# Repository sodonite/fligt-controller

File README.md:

Flight Controller
This is a custom flight controller engineered specifically for rocket stabilization and control. Powered by an STM32F722 microcontroller, it incorporates an ICM-45686 IMU alongside a BMP580 barometer, with an integrated microSD card slot dedicated to flight telemetry logging. The board supports 2S LiPo battery configurations featuring onboard charging functionality, as well as dedicated PWM output channels for servo actuation.

Designed in KiCad, the entire project is completely open source.

PCB:

3D Image:

Schematic:

Technical Specifications
Brain: STM32F722RET6 microcontroller.
IMU: ICM-45686 high-precision motion sensor.
Barometer: BMP580 altitude tracker.
Actuation: Multi-channel servo output via PWM.
Data Logging: Onboard MicroSD card slot.
Power Management:
BQ25883: 2-cell LiPo battery charger via USB-C.
TPS63070: 5V Buck-Boost regulator for servos.
LMR51430: 3.3V Buck regulator for the MCU and sensors.
D2: RGB LED (Common Anode) — Visual status indicator for system initialization, ready-to-fly state, and critical error reporting (IMU, battery, SD card, and power rails).

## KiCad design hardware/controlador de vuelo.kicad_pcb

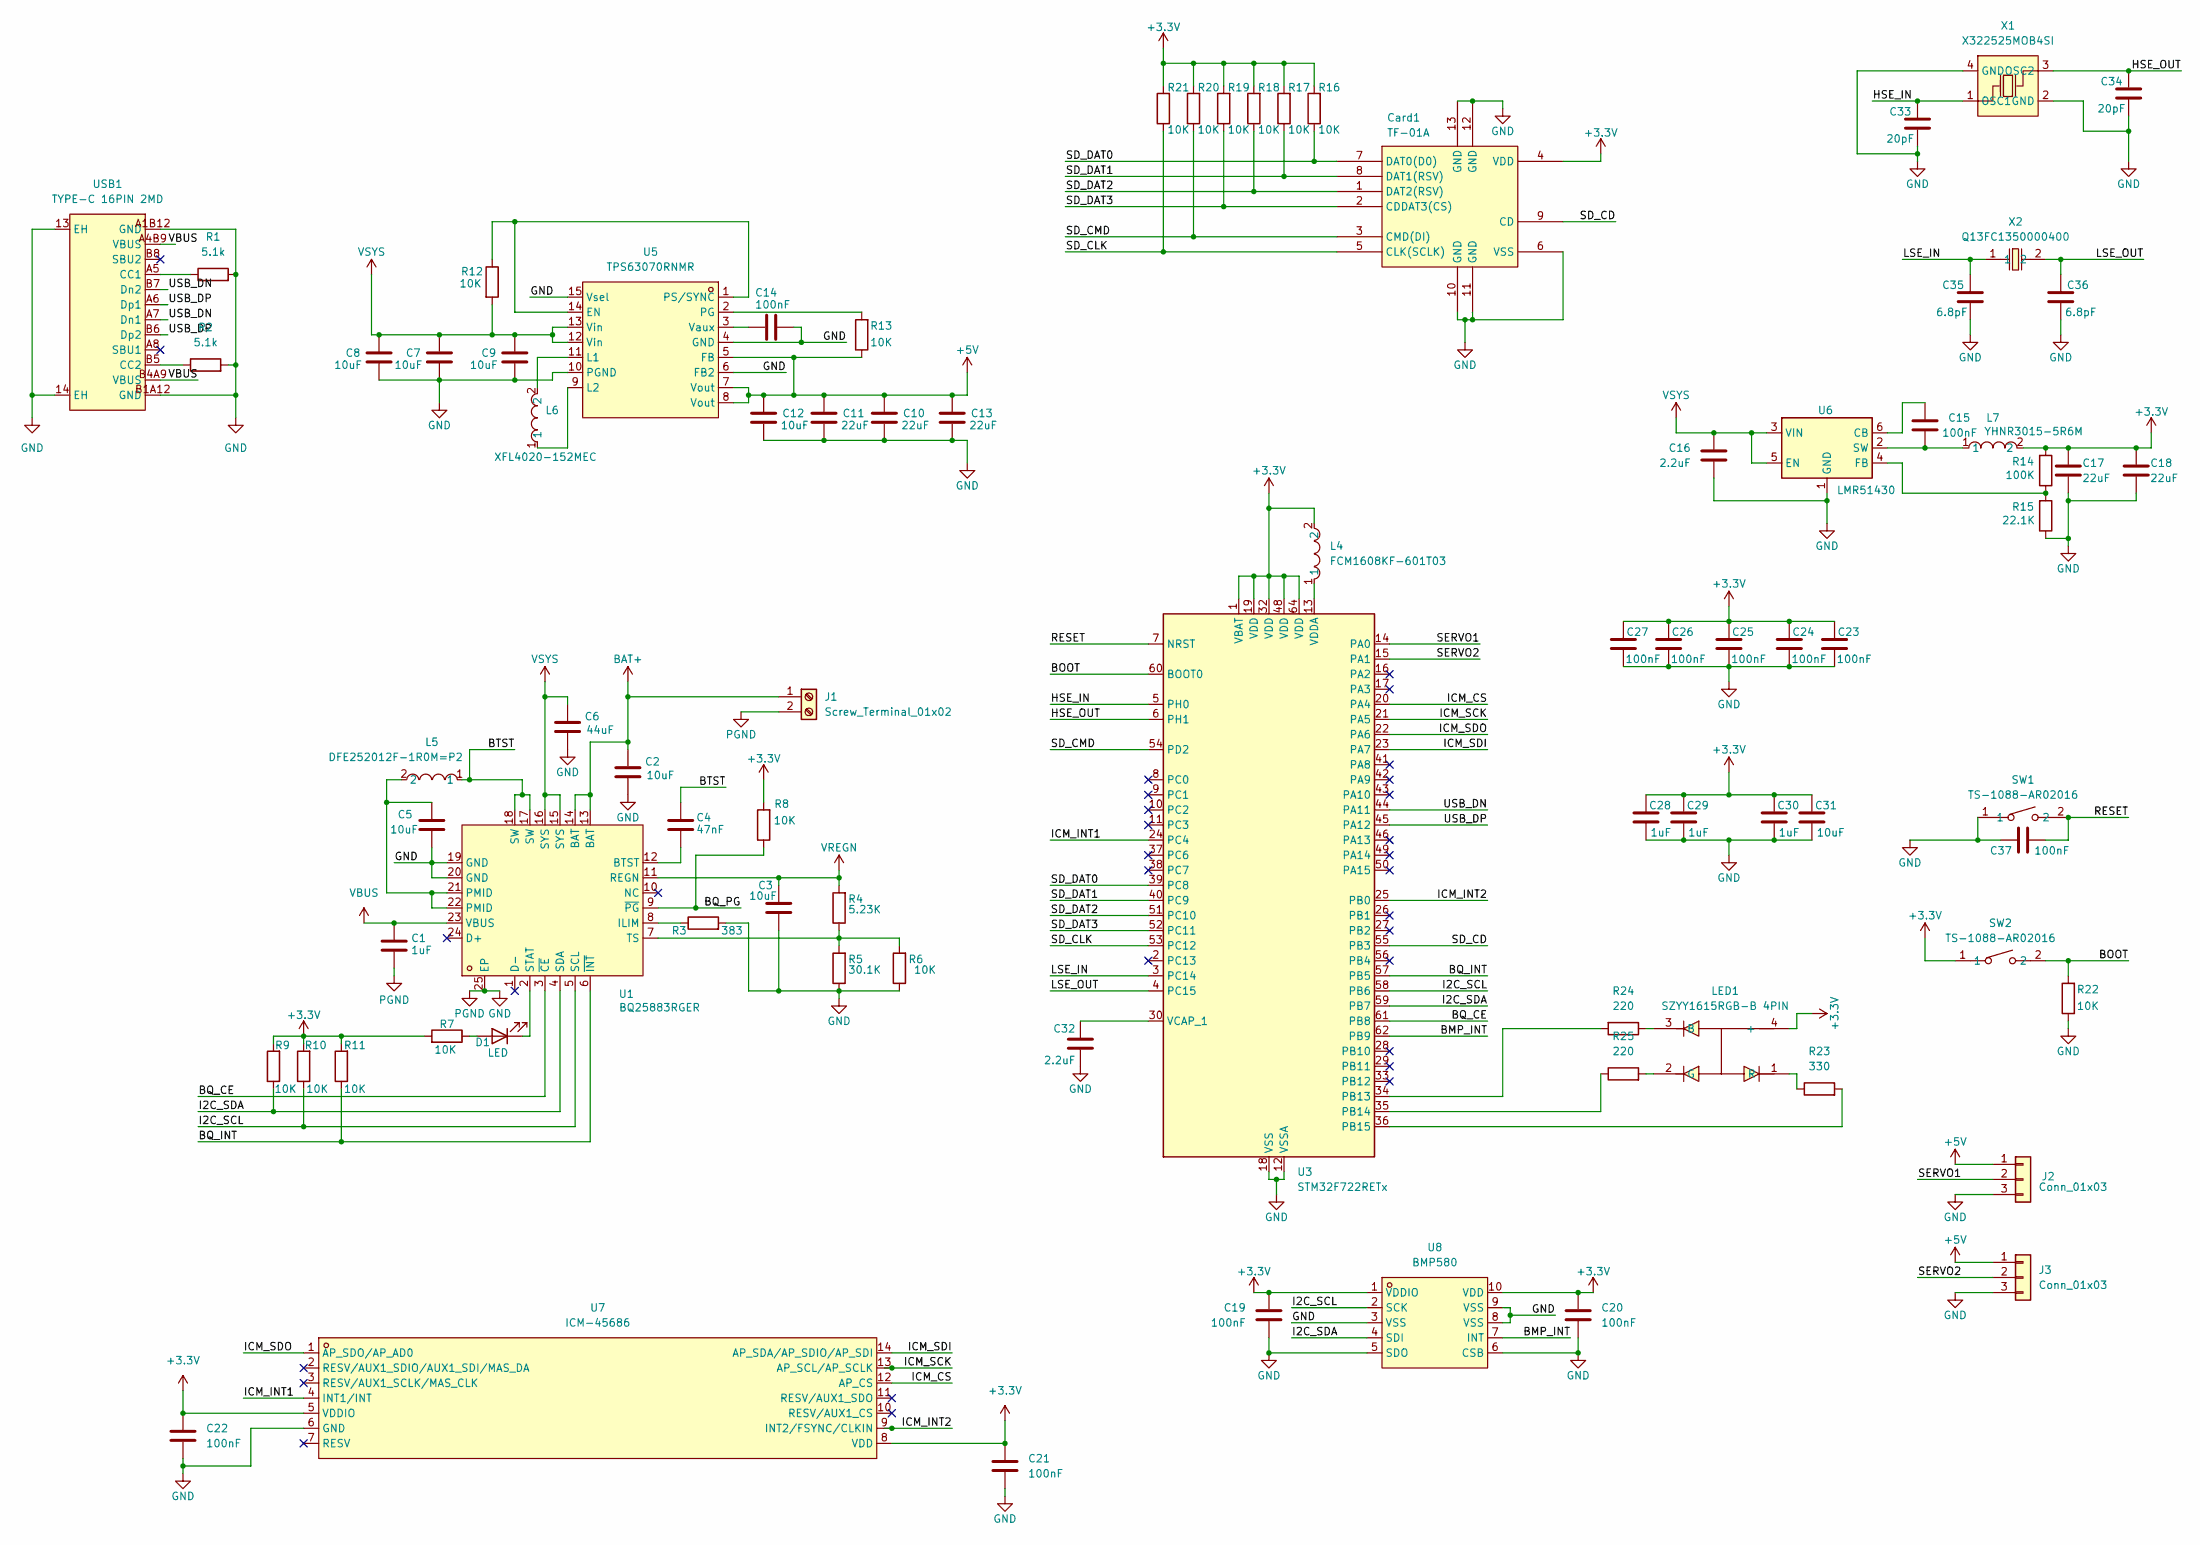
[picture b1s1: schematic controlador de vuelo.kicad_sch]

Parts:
C1, C28, C29, C30: 1uF; C_0402_1005Metric
C2, C9, C12: 10uF; C_0603_1608Metric
C3, C5, C31: 10uF; C_0402_1005Metric
C4: 47nF; C_0201_0603Metric
C6: 44uF; C_0603_1608Metric
C7, C8: 10uF; C_0805_2012Metric
C10, C11, C13: 22uF; C_0805_2012Metric
C14, C15, C19, C20, C21, C22, C23, C24, C25, C26, C27, C37: 100nF; C_0201_0603Metric
C16: 2.2uF; C_0603_1608Metric
C17, C18: 22uF; C_0402_1005Metric
C32: 2.2uF; C_0201_0603Metric
C33, C34: 20pF; C_0201_0603Metric
C35, C36: 6.8pF; C_0201_0603Metric
Card1: TF-01A; TF-SMD_TF-01A; LCSC Part C91145
D1: LED; LED_0402_1005Metric
J1: Screw_Terminal_01x02; TerminalBlock_Xinya_XY308-2.54-2P_1x02_P2.54mm_Horizontal
J2, J3: Conn_01x03; PinHeader_1x03_P2.54mm_Vertical
L4: FCM1608KF-601T03; L0603; LCSC Part C141723
L5: DFE252012F-1R0M=P2; L2520; LCSC Part C435392
L6: XFL4020-152MEC; IND-SMD_L4.0-W4.0-A; LCSC Part C3033018
L7: YHNR3015-5R6M; IND-SMD_L3.0-W3.0; LCSC Part C18236327
LED1: SZYY1615RGB-B 4PIN; LED-SMD_4P-L1.6-W1.5-TR-1; MPN SZYY1615RGB-B 4pin; LCSC Part C3029071
R1, R2: 5.1k; R_0201_0603Metric
R3: 383; R_0201_0603Metric
R4: 5.23K; R_0201_0603Metric
R5: 30.1K; R_0201_0603Metric
R6, R7, R8, R9, R10, R11, R12, R13, R16, R17, R18, R19, R20, R21, R22: 10K; R_0201_0603Metric
R14: 100K; R_0402_1005Metric
R15: 22.1K; R_0402_1005Metric
R23: 330; R_0201_0603Metric
R24, R25: 220; R_0201_0603Metric
SW1, SW2: TS-1088-AR02016; SW-SMD_L3.9-W3.0-P4.45; LCSC Part C720477
U1: BQ25883RGER; VFQFPN-24_L4.0-W4.0-P0.50-BL-EP2.8; LCSC Part C544362
U3: STM32F722RETx; LQFP-64_10x10mm_P0.5mm
U5: TPS63070RNMR; VQFN-HR-15_L3.0-W2.5-P0.50-BL_TPS63070RNMR; LCSC Part C109322
U6: LMR51430; SOT-23-6
U7: ICM-45686; LGA-14_L3.0-W2.5-P0.50-TL; LCSC Part C22459454
U8: BMP580; LGA-10_L2.0-W2.0-P0.50-TL_BMP580; LCSC Part C22391138
USB1: TYPE-C 16PIN 2MD; USB-C-SMD_TYPE-C-16PIN-2MD-073; MPN TYPE-C 16PIN 2MD(073); LCSC Part C2765186
X1: X322525MOB4SI; CRYSTAL-SMD_4P-L3.2-W2.5-BL; LCSC Part C9006
X2: Q13FC1350000400; FC-135R_L3.2-W1.5; LCSC Part C32346

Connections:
+3.3V: C17.1, C18.1, C19.1, C20.1, C21.1, C22.1, C23.1, C24.1, C25.1, C26.1, C27.1, C28.1, C29.1, C30.1, C31.1, Card1.4 (VDD), L4.2, L7.2, LED1.4 (+), R7.2, R8.2, R9.2, R10.2, R11.2, R14.2, R16.2, R17.2, R18.2, R19.2, R20.2, R21.2, SW2.1, U3.1 (VBAT), U3.19 (VDD), U3.32 (VDD), U3.48 (VDD), U3.64 (VDD), U7.5 (VDDIO), U7.8 (VDD), U8.1 (VDDIO), U8.10 (VDD)
+5V: C10.1, C11.1, C12.1, C13.1, J2.1, J3.1, R13.1, U5.5 (FB), U5.7 (Vout), U5.8 (Vout)
/BMP_INT: U3.62 (PB9), U8.7 (INT)
/BOOT: R22.2, SW2.2, U3.60 (BOOT0)
/BQ_CE: U1.3 (~CE), U3.61 (PB8)
/BQ_INT: R11.1, U1.6 (~INT), U3.57 (PB5)
/BQ_PG: R8.1, U1.9 (~PG)
/BTST: C4.1, L5.1, U1.17 (SW), U1.18 (SW)
/HSE_IN: C33.1, U3.5 (PH0), X1.1 (OSC1)
/HSE_OUT: C34.1, U3.6 (PH1), X1.3 (OSC2)
/I2C_SCL: R10.1, U1.5 (SCL), U3.58 (PB6), U8.2 (SCK)
/I2C_SDA: R9.1, U1.4 (SDA), U3.59 (PB7), U8.4 (SDI)
/ICM_CS: U3.20 (PA4), U7.12 (AP_CS)
/ICM_INT1: U3.24 (PC4), U7.4 (INT1/INT)
/ICM_INT2: U3.25 (PB0), U7.9 (INT2/FSYNC/CLKIN)
/ICM_SCK: U3.21 (PA5), U7.13 (AP_SCL/AP_SCLK)
/ICM_SDI: U3.23 (PA7), U7.14 (AP_SDA/AP_SDIO/AP_SDI)
/ICM_SDO: U3.22 (PA6), U7.1 (AP_SDO/AP_AD0)
/LSE_IN: C35.1, U3.3 (PC14), X2.1
/LSE_OUT: C36.1, U3.4 (PC15), X2.2
/RESET: C37.2, SW1.2, U3.7 (NRST)
/SD_CD: Card1.9 (CD), U3.55 (PB3)
/SD_CLK: Card1.5 (CLK(SCLK)), R21.1, U3.53 (PC12)
/SD_CMD: Card1.3 (CMD(DI)), R20.1, U3.54 (PD2)
/SD_DAT0: Card1.7 (DAT0(D0)), R16.1, U3.39 (PC8)
/SD_DAT1: Card1.8 (DAT1(RSV)), R17.1, U3.40 (PC9)
/SD_DAT2: Card1.1 (DAT2(RSV)), R18.1, U3.51 (PC10)
/SD_DAT3: Card1.2 (CDDAT3(CS)), R19.1, U3.52 (PC11)
/SERVO1: J2.2, U3.14 (PA0)
/SERVO2: J3.2, U3.15 (PA1)
/USB_DN: U3.44 (PA11), USB1.A7 (Dn1), USB1.B7 (Dn2)
/USB_DP: U3.45 (PA12), USB1.A6 (Dp1), USB1.B6 (Dp2)
BAT+: C2.1, J1.1, U1.13 (BAT), U1.14 (BAT)
GND: C1.2, C2.2, C3.2, C5.2, C6.2, C7.2, C8.2, C9.2, C10.2, C11.2, C12.2, C13.2, C14.2, C16.2, C17.2, C18.2, C19.2, C20.2, C21.2, C22.2, C23.2, C24.2, C25.2, C26.2, C27.2, C28.2, C29.2, C30.2, C31.2, C32.2, C33.2, C34.2, C35.2, C36.2, C37.1, Card1.6 (VSS), Card1.10 (GND), Card1.11 (GND), Card1.12 (GND), Card1.13 (GND), J1.2, J2.3, J3.3, R1.2, R2.2, R3.2, R5.1, R6.1, R15.1, R22.1, SW1.1, U1.19 (GND), U1.20 (GND), U1.25 (EP), U3.12 (VSSA), U3.18 (VSS), U3.31 (VSS), U3.47 (VSS), U3.63 (VSS), U5.4 (GND), U5.6 (FB2), U5.10 (PGND), U5.15 (Vsel), U6.1 (GND), U7.6 (GND), U8.3 (VSS), U8.5 (SDO), U8.6 (CSB), U8.8 (VSS), U8.9 (VSS), USB1.13 (EH), USB1.14 (EH), USB1.A1B12 (GND), USB1.B1A12 (GND), X1.2 (GND), X1.4 (GND)
unnamed: C5.1, L5.2, U1.21 (PMID), U1.22 (PMID)
unnamed: D1.2 (A), R7.1
unnamed: D1.1 (K), U1.2 (STAT)
unnamed: LED1.3 (B), R24.1
unnamed: LED1.2 (G), R25.2
unnamed: LED1.1 (R), R23.1
unnamed: C4.2, U1.12 (BTST)
unnamed: R3.1, U1.8 (ILIM)
unnamed: R4.1, R5.2, R6.2, U1.7 (TS)
unnamed: R24.2, U3.34 (PB13)
unnamed: R25.1, U3.35 (PB14)
unnamed: R23.2, U3.36 (PB15)
unnamed: C32.1, U3.30 (VCAP_1)
unnamed: L4.1, U3.13 (VDDA)
unnamed: R12.1, U5.1 (PS/SYNC), U5.14 (EN)
unnamed: L6.2, U5.11 (L1)
unnamed: L6.1, U5.9 (L2)
unnamed: R13.2, U5.2 (PG)
unnamed: C14.1, U5.3 (Vaux)
unnamed: C15.1, U6.6 (CB)
unnamed: R14.1, R15.2, U6.4 (FB)
unnamed: C15.2, L7.1, U6.2 (SW)
unnamed: R1.1, USB1.A5 (CC1)
unnamed: R2.1, USB1.B5 (CC2)
VBUS: C1.1, U1.23 (VBUS), USB1.A4B9 (VBUS), USB1.B4A9 (VBUS)
VREGN: C3.1, R4.2, U1.11 (REGN)
VSYS: C6.1, C7.1, C8.1, C9.1, C16.1, R12.2, U1.15 (SYS), U1.16 (SYS), U5.12 (Vin), U5.13 (Vin), U6.3 (VIN), U6.5 (EN)

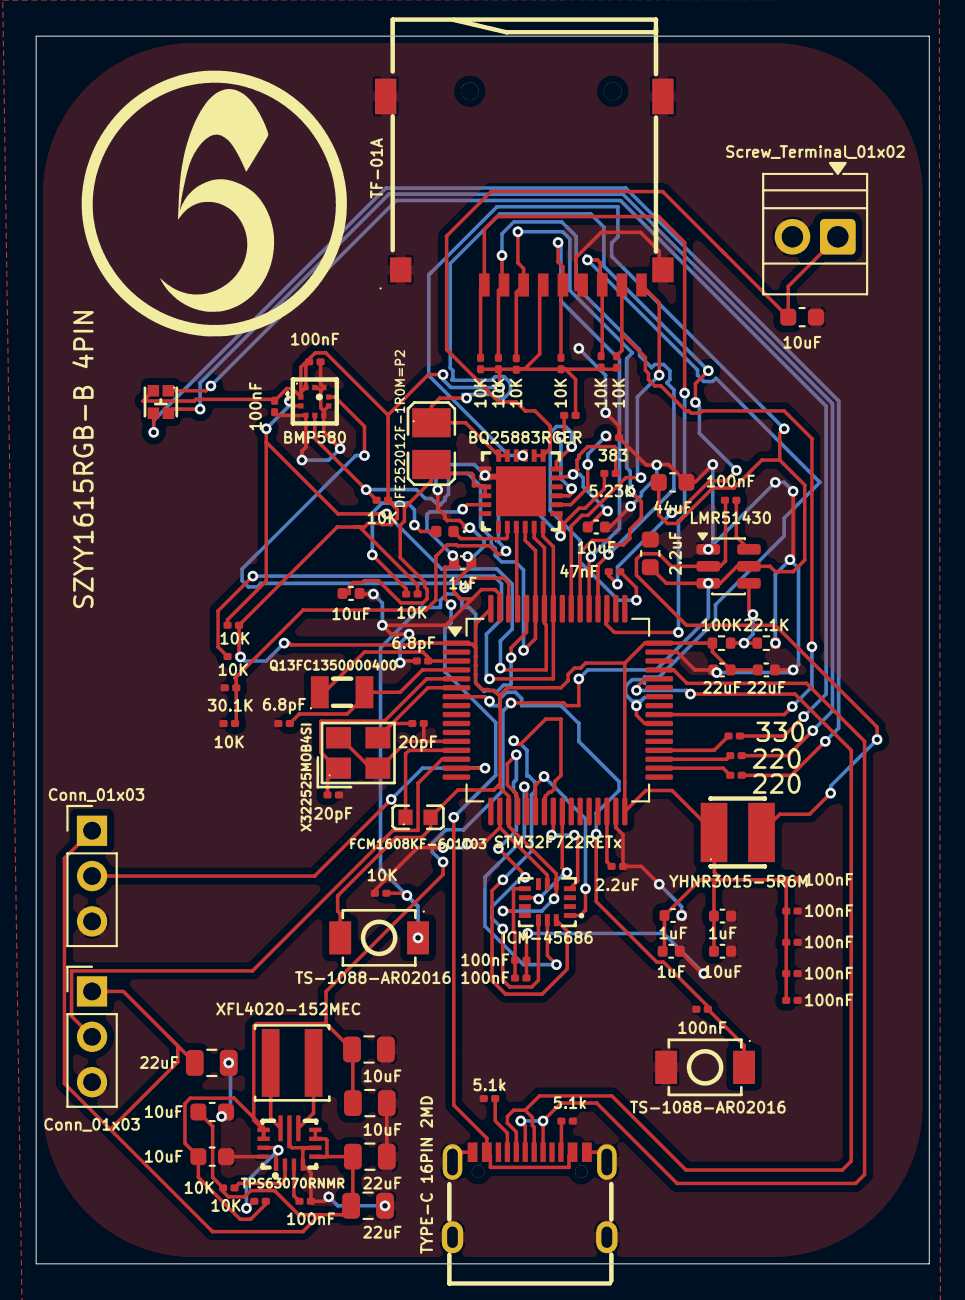
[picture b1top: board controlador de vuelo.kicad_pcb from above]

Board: 2 copper layers, 50.0 x 68.7 mm, 83 parts (0 on the bottom side), 61 nets.

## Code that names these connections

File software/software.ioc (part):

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Mcu.Name=STM32F722R(C-E)Tx
Mcu.Package=LQFP64
Mcu.UserName=STM32F722RETx
PA0-WKUP.Signal=S_TIM2_CH1_ETR
PA1.Signal=S_TIM2_CH2
PA11.Mode=Host_Only
PA11.Signal=USB_OTG_FS_DM
PA12.Mode=Host_Only
PA12.Signal=USB_OTG_FS_DP
PA4.Mode=NSS_Signal_Hard_Output
PA4.Signal=SPI1_NSS
PA5.Mode=Full_Duplex_Master
PA5.Signal=SPI1_SCK
PA6.Mode=Full_Duplex_Master
PA6.Signal=SPI1_MISO
PA7.Mode=Full_Duplex_Master
PA7.Signal=SPI1_MOSI
PB0.Signal=GPXTI0
PB13.GPIOParameters=GPIO_Speed,PinState,GPIO_PuPd,GPIO_Label
PB13.GPIO_Label=LED_B
PB13.GPIO_PuPd=GPIO_NOPULL
PB13.GPIO_Speed=GPIO_SPEED_FREQ_HIGH
PB13.PinState=GPIO_PIN_SET
PB13.Signal=GPIO_Output
PB14.GPIOParameters=GPIO_Speed,PinState,GPIO_Label
PB14.GPIO_Label=LED_G 
PB14.GPIO_Speed=GPIO_SPEED_FREQ_HIGH
PB14.PinState=GPIO_PIN_SET
PB14.Signal=GPIO_Output
PB15.GPIOParameters=GPIO_Speed,PinState,GPIO_Label
PB15.GPIO_Label=LED_R
PB15.GPIO_Speed=GPIO_SPEED_FREQ_HIGH
PB15.PinState=GPIO_PIN_SET
PB15.Signal=GPIO_Output
PB3.Signal=GPIO_Input
PB5.Signal=GPXTI5
PB6.Mode=I2C
PB6.Signal=I2C1_SCL
PB7.Mode=I2C
PB7.Signal=I2C1_SDA
PB8.Signal=GPIO_Output
PB9.Signal=GPXTI9
PC10.Mode=SD_4_bits_Wide_bus
PC10.Signal=SDMMC1_D2
PC11.Mode=SD_4_bits_Wide_bus
PC11.Signal=SDMMC1_D3
PC12.Mode=SD_4_bits_Wide_bus
PC12.Signal=SDMMC1_CK
PC14-OSC32_IN.Mode=LSE-External-Oscillator
PC14-OSC32_IN.Signal=RCC_OSC32_IN
PC15-OSC32_OUT.Mode=LSE-External-Oscillator
PC15-OSC32_OUT.Signal=RCC_OSC32_OUT
PC4.Signal=GPXTI4
PC8.Mode=SD_4_bits_Wide_bus
PC8.Signal=SDMMC1_D0
PC9.Mode=SD_4_bits_Wide_bus
PC9.Signal=SDMMC1_D1
PD2.Mode=SD_4_bits_Wide_bus
PD2.Signal=SDMMC1_CMD
PH0-OSC_IN.Mode=HSE-External-Oscillator
PH0-OSC_IN.Signal=RCC_OSC_IN
PH1-OSC_OUT.Mode=HSE-External-Oscillator
PH1-OSC_OUT.Signal=RCC_OSC_OUT
RCC.HSE_VALUE=25000000
board=custom
